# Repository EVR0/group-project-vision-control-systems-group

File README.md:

# Team 2 Final Project
# Smart Car Redesign and Vision-Based Autonomous Navigation

Course: Artificial Intelligence Systems Engineering Design I

Instructor: Dr. Shaimaa Ali

Date: April 3, 2026

Group: Team 2

Team members:
- Evan Romano (251327329)
- Joseph Toma (251283541)
- Mohammed Alamen Qassab (251285296)

## Project Summary

For this project, we redesigned the Freenove 4WD Smart Car to reduce mechanical complexity and improve autonomous performance. The original platform was modified to use front-wheel tank drive, a fixed camera mount, and a fixed ultrasonic mount. On the software side, we implemented AprilTag-based localization and goal navigation, with obstacle avoidance always taking priority.

Our final system combines perception, control, and actuation in one loop:
- Camera-based AprilTag detection and pose estimation
- Board-frame localization
- Path planning and path following
- Ultrasonic obstacle detection and avoidance
- Differential motor control

## Software Layout

The final code used for this project is in the Code folder.

Main runtime files include:
- Code/main.py
- Code/config.py
- Code/detector.py
- Code/localization.py
- Code/pathfinder.py
- Code/controller.py
- Code/motor_adapter.py
- Code/ultrasonic.py
- Code/obstacle_avoider.py

Testing scripts include:
- Code/test_detect.py
- Code/test_motors.py
- Code/test_turn.py
- Code/test_ultrasonic.py
- Code/test_ultrasonic_driving.py

An earlier sprint implementation is included in Code/Sprint2 Code.

## How We Run It

From the repository root, go to the code folder:
cd Code

List available tags:
python3 main.py --list

Run detection-only mode:
python3 main.py --test

Navigate to a target tag:
python3 main.py <TAG_ID>

Navigate to explicit coordinates:
python3 main.py --xy <X_M> <Y_M> [YAW_DEG]

Run subsystem tests:
python3 test_motors.py
python3 test_ultrasonic.py
python3 test_ultrasonic_driving.py
python3 test_detect.py
python3 test_turn.py

## Hardware and Dependencies

Hardware used:
- Raspberry Pi with CSI camera
- Freenove motor electronics stack
- HC-SR04 ultrasonic sensor

Ultrasonic pin mapping in our configuration:
- Trigger: GPIO 27
- Echo: GPIO 22

Main software dependencies:
- OpenCV
- NumPy
- Picamera2
- RPi.GPIO
- SMBus
- AprilTag library (dt-apriltags or pyapriltags)

## Other Project Assets

This repository also includes:
- CAD files and print files for mechanical redesign
- PCB design files and fabrication outputs
- Formal documentation (proposal, sprint reports, final report, presentation)
- Meeting minutes
- Photos and videos from testing and demonstrations

Note on PCB:
The PCB was designed during the project, but it was not integrated into the final robot due to time constraints.

## Final Notes

The complete design rationale, implementation details, testing process, and future work are documented in the final report in the Documentation folder.

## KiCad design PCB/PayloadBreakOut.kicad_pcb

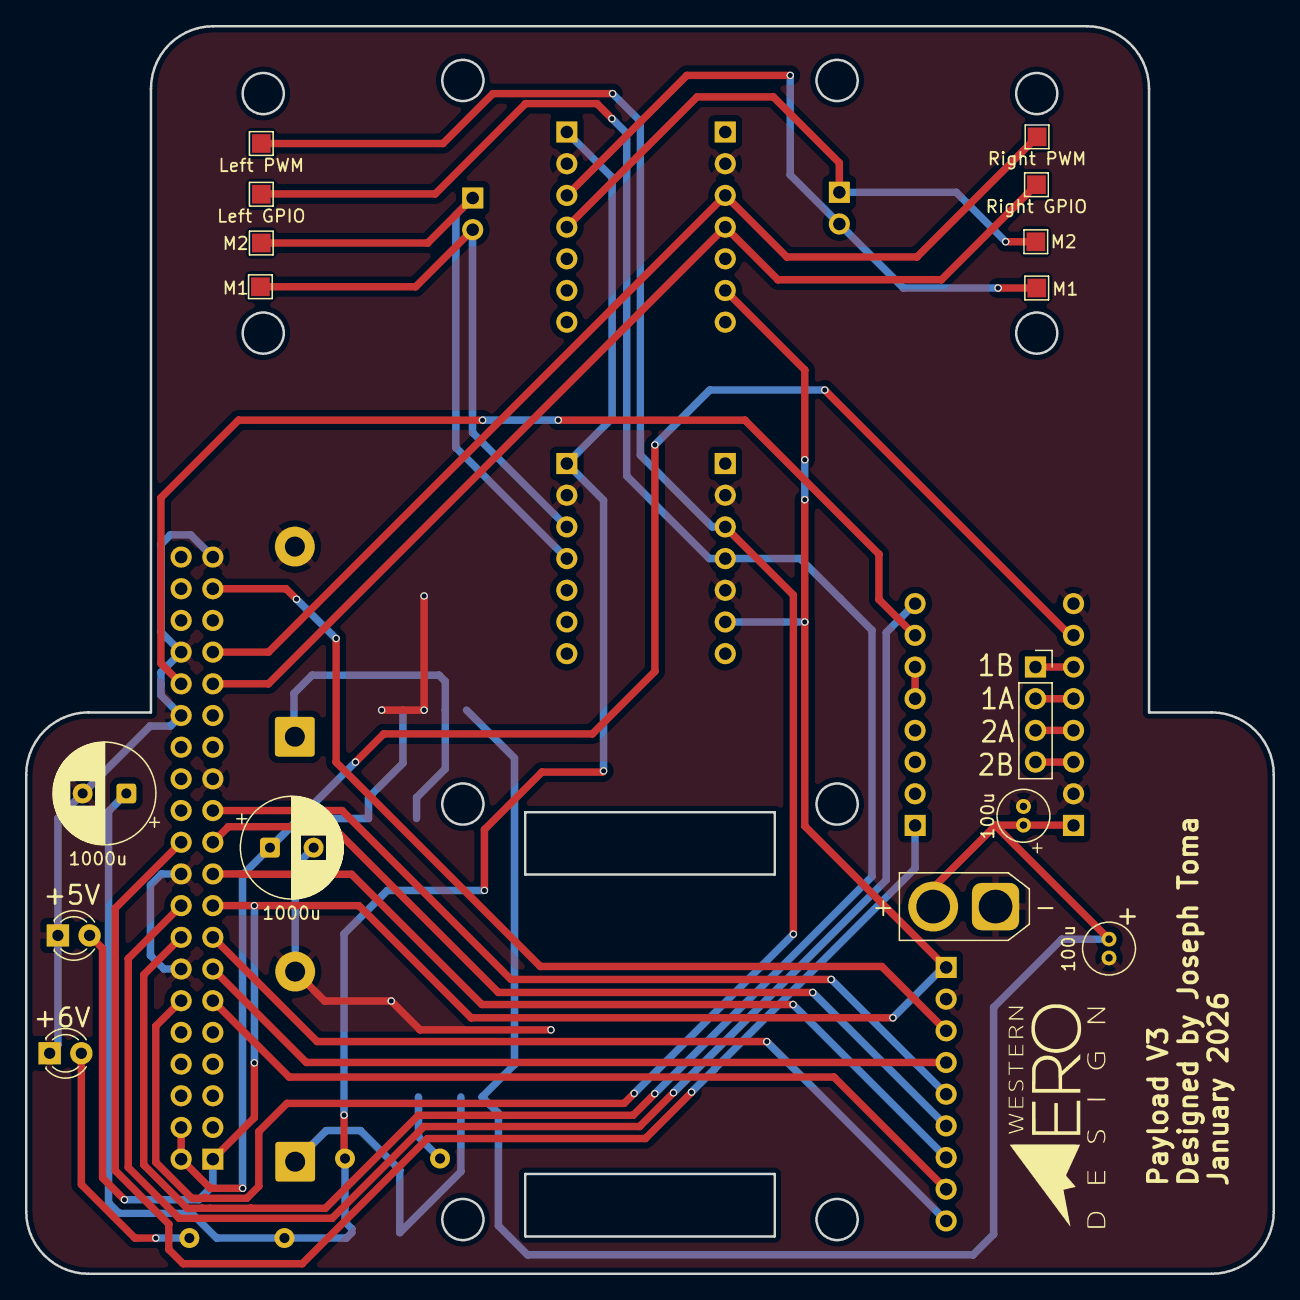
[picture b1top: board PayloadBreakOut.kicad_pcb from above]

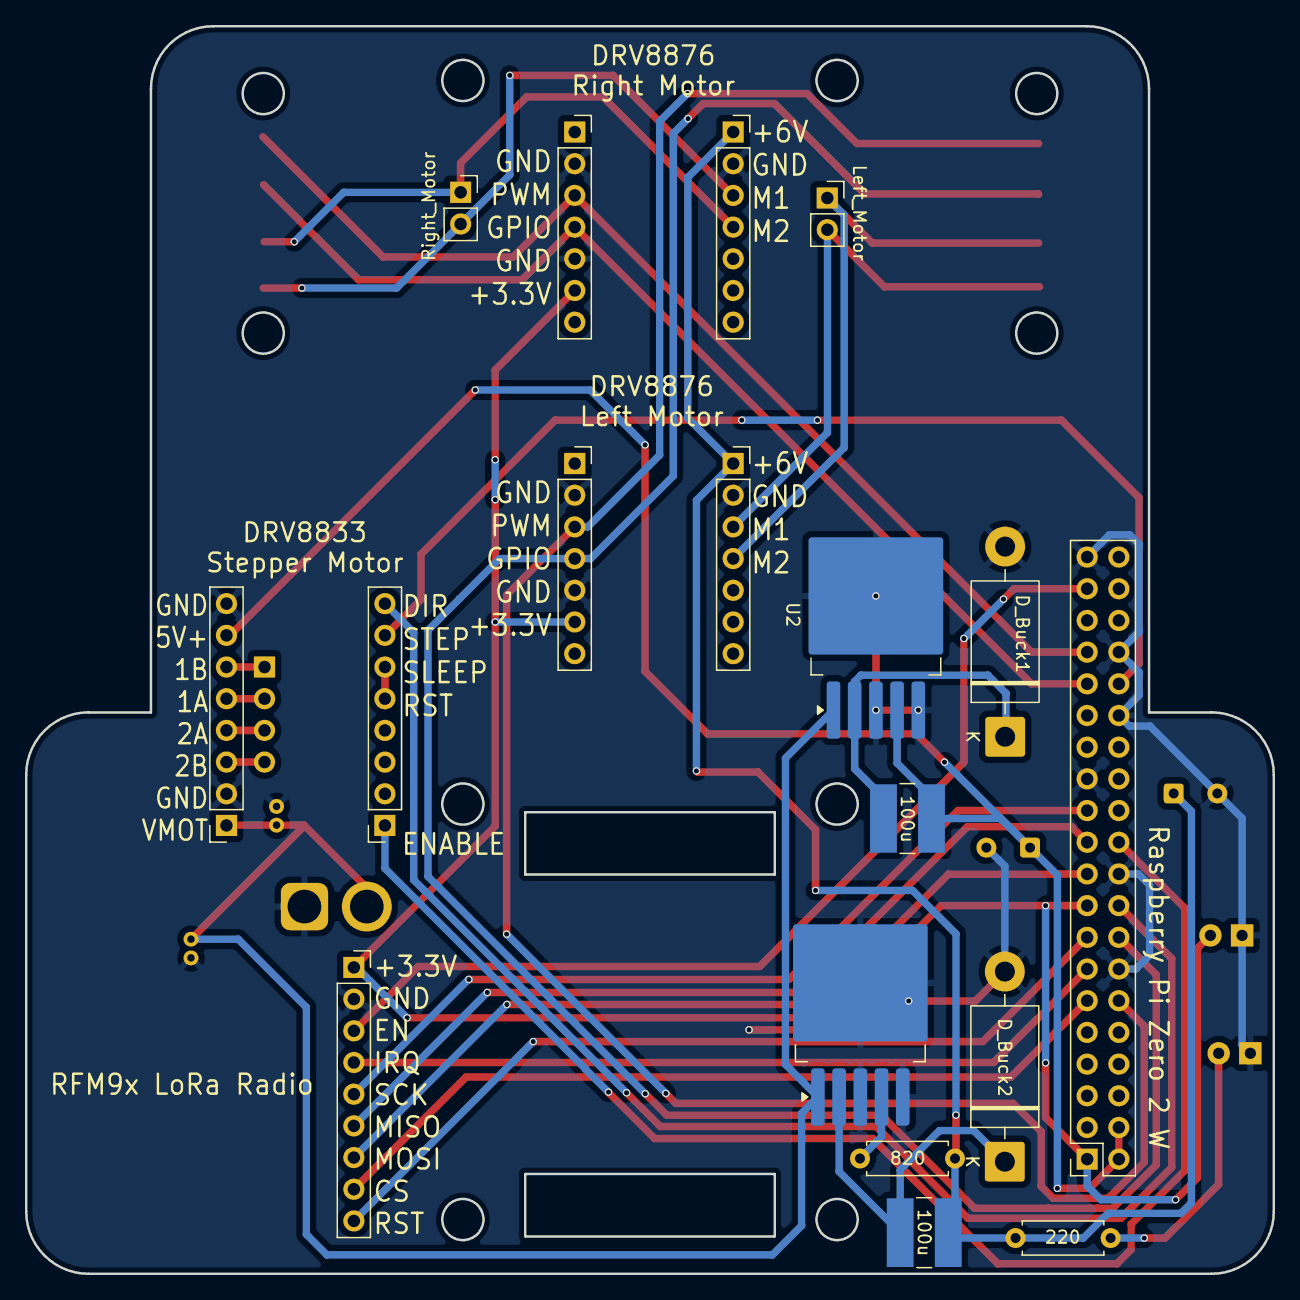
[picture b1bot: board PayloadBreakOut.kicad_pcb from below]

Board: 2 copper layers, 100.0 x 100.0 mm, 34 parts (18 on the bottom side), 32 nets.

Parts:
C1: 100u; C_Radial_D4.0mm_H5.0mm_P1.50mm
C_Pol1: 100u; C_Radial_D4.0mm_H5.0mm_P1.50mm
C_Pol2, C_Pol3: 1000u; CP_Radial_D8.0mm_P3.50mm
D_Buck1, D_Buck2: 1N5822; D_DO-201AD_P15.24mm_Horizontal
J1: N20_Left_Motor_Left; PinSocket_1x07_P2.54mm_Vertical
J2: N20_Right_Motor_Left; PinSocket_1x07_P2.54mm_Vertical
J3: Left_Motor; PinSocket_1x02_P2.54mm_Vertical
J4: Right_Motor; PinSocket_1x02_P2.54mm_Vertical
J5: N20_Left_Motor_Right; PinSocket_1x07_P2.54mm_Vertical
J6: N20_Right_Motor_Right; PinSocket_1x07_P2.54mm_Vertical
J7, J11: Conn_01x02; LED_D3.0mm_FlatTop
J8: Stepper_Motor_Left; PinSocket_1x08_P2.54mm_Vertical
J9: Stepper_Motor; PinSocket_1x04_P2.54mm_Vertical
J10: Stepper_Motor_Right; PinSocket_1x08_P2.54mm_Vertical
L_Buck1, L_Buck2: 100u; L_TracoPower_TCK-047_5.2x5.8mm
PWR1: Conn_01x02; AMASS_XT30U-F_1x02_P5.0mm_Vertical
R1: 820; R_Axial_DIN0207_L6.3mm_D2.5mm_P7.62mm_Horizontal
R2: 220; R_Axial_DIN0207_L6.3mm_D2.5mm_P7.62mm_Horizontal
RPI1: Conn_02x20_Odd_Even; PinSocket_2x20_P2.54mm_Vertical
TP1: Right PWM; TestPoint_Pad_1.5x1.5mm
TP2: Left PWM; TestPoint_Pad_1.5x1.5mm
TP3: Left GPIO; TestPoint_Pad_1.5x1.5mm
TP4: Right GPIO; TestPoint_Pad_1.5x1.5mm
TP5, TP6: M1; TestPoint_Pad_1.5x1.5mm
TP7, TP8: M2; TestPoint_Pad_1.5x1.5mm
Trans1: Conn_01x09; PinSocket_1x09_P2.54mm_Vertical
U1, U2: LM2576HVS-5; TO-263-5_TabPin3

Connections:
+3.3V: J1.6, J2.6, J7.2, RPI1.1, RPI1.17, Trans1.1
+5V: C_Pol2.1, J10.7, L_Buck1.2, RPI1.2, RPI1.4, U2.4 (FB)
+6V: C_Pol3.1, J5.1, J6.1, L_Buck2.2, R1.2, R2.1
/CS: RPI1.11, Trans1.8
/EN: RPI1.37, Trans1.3
/IRQ: RPI1.13, Trans1.4
/Left_GPIO: J1.4, RPI1.16, TP3.1
/Left_PWM: J1.3, RPI1.12, TP2.1
/MISO: RPI1.21, Trans1.6
/MOSI: RPI1.19, Trans1.7
/RST: RPI1.15, Trans1.9
/Right_GPIO: J2.4, RPI1.31, TP4.1
/Right_PWM: J2.3, RPI1.33, TP1.1
/SCK: RPI1.23, Trans1.5
/Stepper_Dir: J8.8, RPI1.18
/Stepper_Enable: J8.1, RPI1.22
/Stepper_Step: J8.7, RPI1.32
GND: C1.2, C_Pol1.2, C_Pol2.2, C_Pol3.2, D_Buck1.2 (A), D_Buck2.2 (A), J1.2, J1.5, J2.2, J2.5, J5.2, J6.2, J7.1, J10.2, J10.8, J11.1, PWR1.1, RPI1.14, RPI1.20, RPI1.25, RPI1.30, RPI1.34, RPI1.39, Trans1.2, U1.3 (GND), U1.5 (~ON/OFF), U2.3 (GND), U2.5 (~ON/OFF)
unnamed: D_Buck1.1 (K), L_Buck1.1, U2.2 (OUT)
unnamed: D_Buck2.1 (K), L_Buck2.1, U1.2 (OUT)
unnamed: J3.1, J5.4, TP7.1
unnamed: J3.2, J5.3, TP5.1
unnamed: J4.1, J6.4, TP8.1
unnamed: J4.2, J6.3, TP6.1
unnamed: J8.5, J8.6
unnamed: J9.4, J10.3
unnamed: J9.3, J10.4
unnamed: J9.2, J10.5
unnamed: J9.1, J10.6
unnamed: J11.2, R2.2
unnamed: R1.1, U1.4 (FB)
VBAT: C1.1, C_Pol1.1, J10.1, PWR1.2, U1.1 (VIN), U2.1 (VIN)
